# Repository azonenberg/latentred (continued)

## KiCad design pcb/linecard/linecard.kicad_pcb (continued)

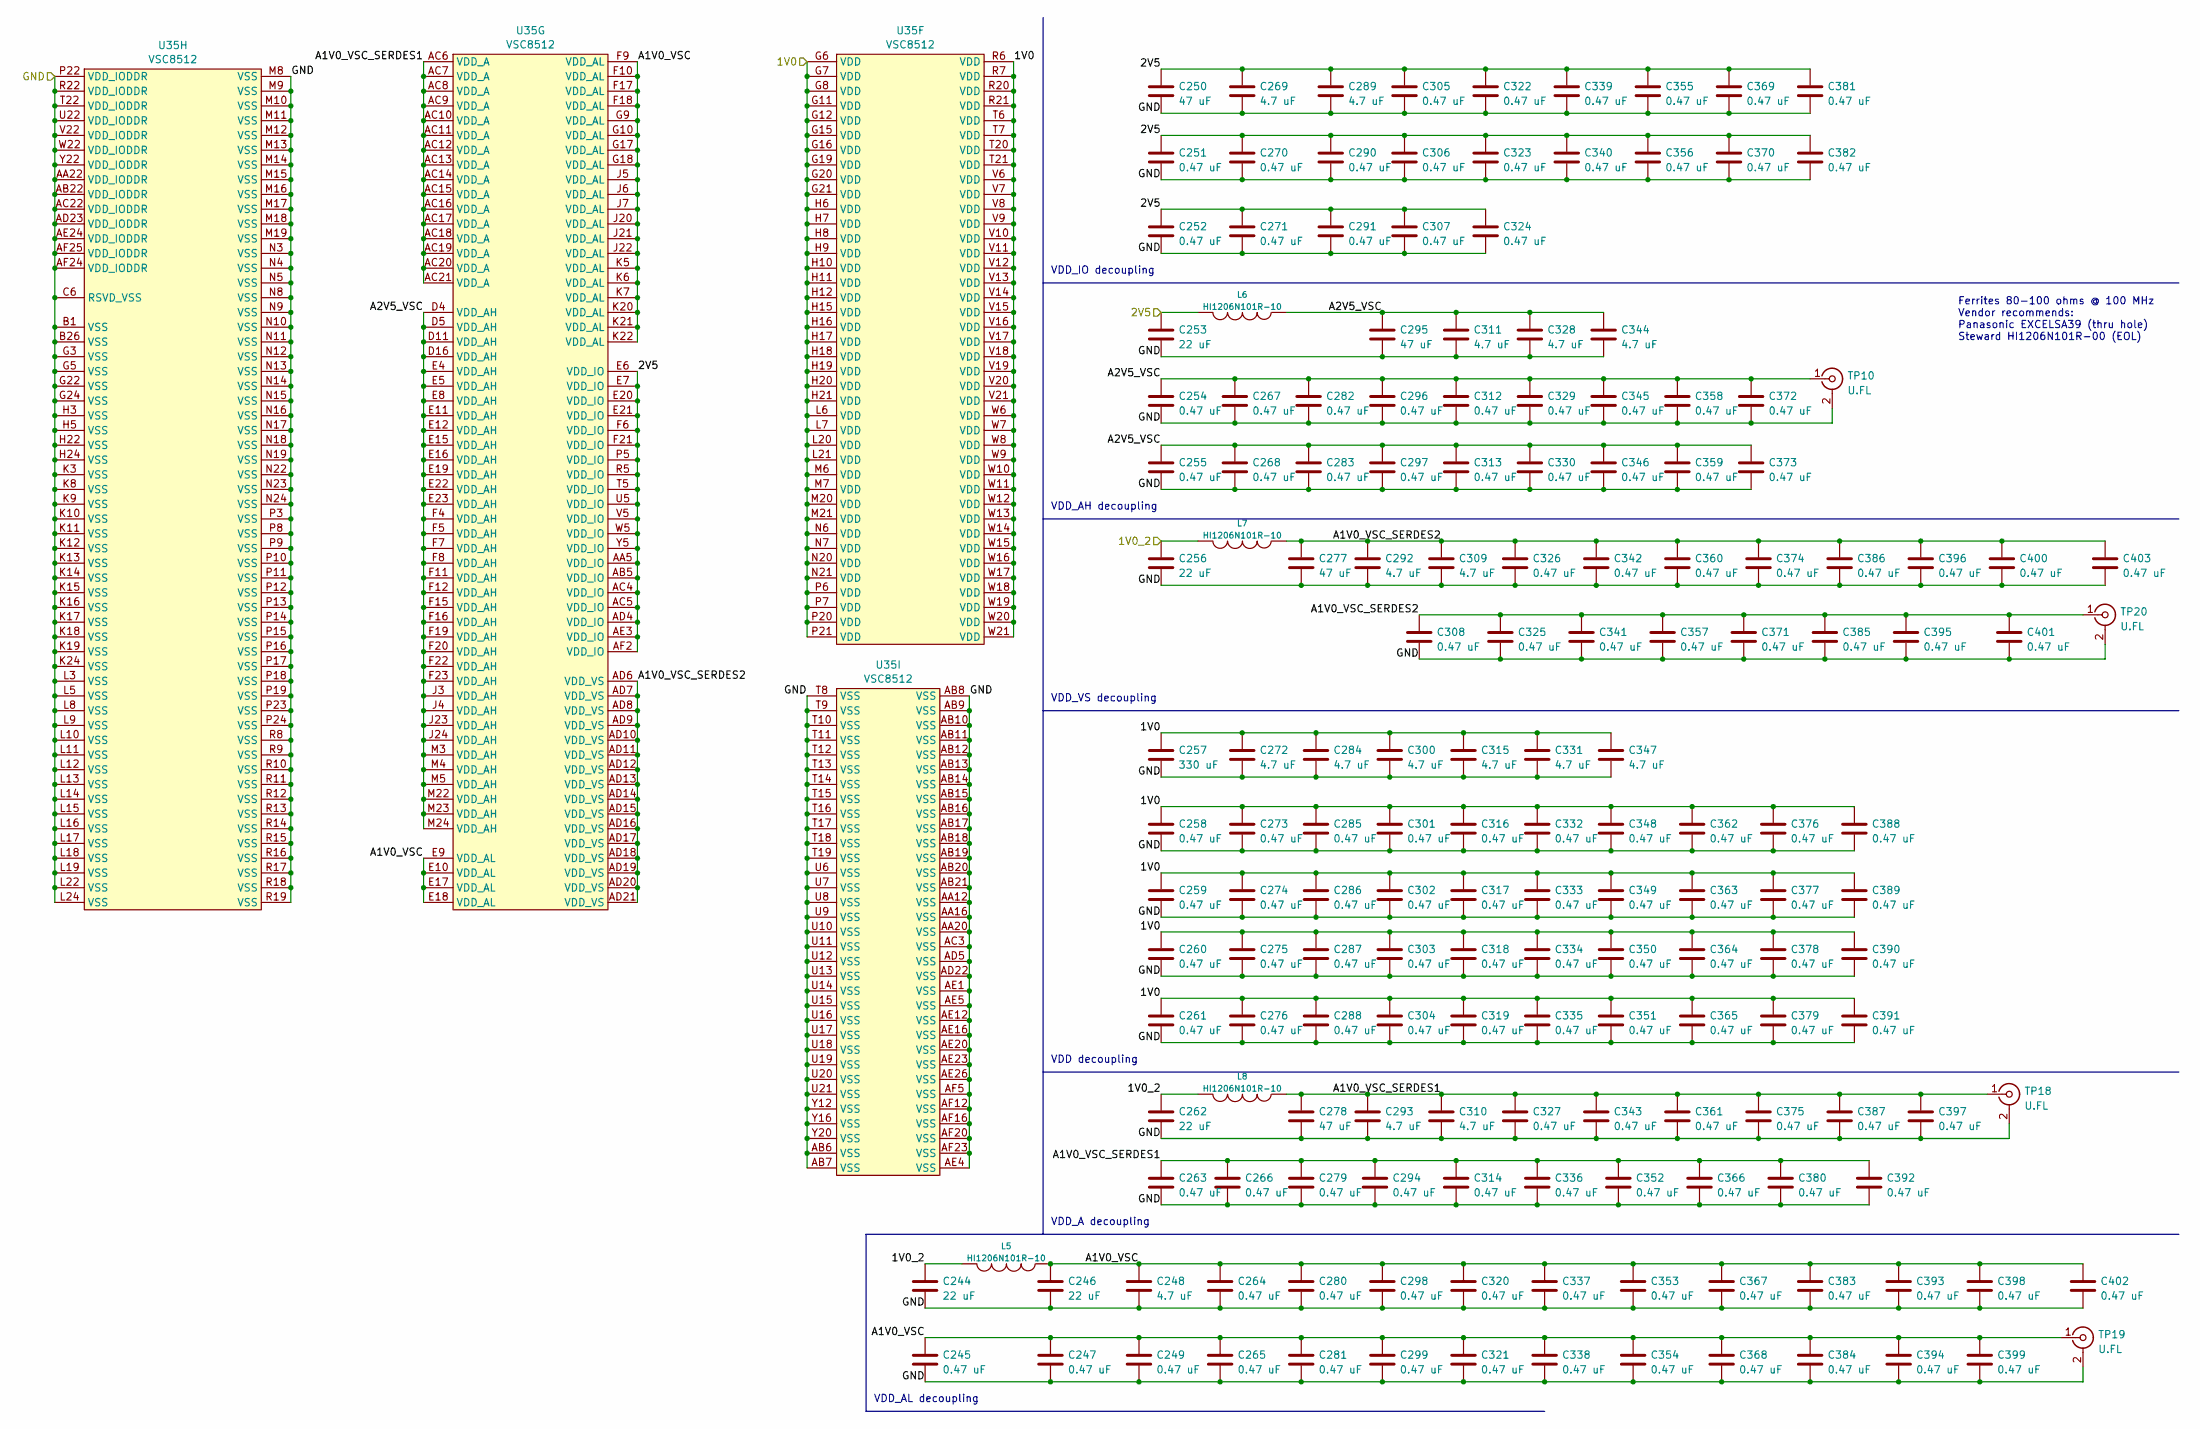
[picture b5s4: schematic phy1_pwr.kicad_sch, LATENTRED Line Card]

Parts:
C244, C246, C256, C262: 22 uF; EIA_0805_CAP_NOSILK
C245, C247, C249, C251, C252, C254, C255, C258, C259, C260, C261, C263, C264, C265, C266, C267, C268, C270, C271, C273, C274, C275, C276, C279, C280, C281, C282, C283, C285, C286, C287, C288, C290, C291, C294, C296, C297, C298, C299, C301, C302, C303, C304, C305, C306, C307, C308, C312, C313, C314, C316, C317, C318, C319, C320, C321, C322, C323, C324, C325, C326, C327, C329, C330, C332, C333, C334, C335, C336, C337, C338, C339, C340, C341, C342, C343, C345, C346, C348, C349, C350, C351, C352, C353, C354, C355, C356, C357, C358, C359, C360, C361, C362, C363, C364, C365, C366, C367, C368, C369, C370, C371, C372, C373, C374, C375, C376, C377, C378, C379, C380, C381, C382, C383, C384, C385, C386, C387, C388, C389, C390, C391, C392, C393, C394, C395, C396, C397, C398, C399, C400, C401, C402, C403: 0.47 uF; EIA_0402_CAP_NOSILK
C248, C269, C272, C284, C289, C292, C293, C300, C309, C310, C311, C315, C328, C331, C344, C347: 4.7 uF; EIA_0603_CAP_NOSILK
C250, C277, C295: 47 uF; EIA_1210_CAP_NOSILK
C253: 22 uF; EIA_1206_CAP_NOSILK
C257: 330 uF; EIA_1210_CAP_NOSILK
C278: 47 uF; EIA_1206_CAP_NOSILK
L5, L6, L7, L8: HI1206N101R-10; EIA_1206_CAP_NOSILK
TP10, TP18, TP19, TP20: U.FL; CONN_U.FL_TE_1909763-1
U35: VSC8512; BGA_676_27x27_FULLARRAY_1MM_FFG676

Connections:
/1V0: C257.1, C258.1, C259.1, C260.1, C261.1, C272.1, C273.1, C274.1, C275.1, C276.1, C284.1, C285.1, C286.1, C287.1, C288.1, C300.1, C301.1, C302.1, C303.1, C304.1, C315.1, C316.1, C317.1, C318.1, C319.1, C331.1, C332.1, C333.1, C334.1, C335.1, C347.1, C348.1, C349.1, C350.1, C351.1, C362.1, C363.1, C364.1, C365.1, C376.1, C377.1, C378.1, C379.1, C388.1, C389.1, C390.1, C391.1, U35.G6 (VDD), U35.G7 (VDD), U35.G8 (VDD), U35.G11 (VDD), U35.G12 (VDD), U35.G15 (VDD), U35.G16 (VDD), U35.G19 (VDD), U35.G20 (VDD), U35.G21 (VDD), U35.H6 (VDD), U35.H7 (VDD), U35.H8 (VDD), U35.H9 (VDD), U35.H10 (VDD), U35.H11 (VDD), U35.H12 (VDD), U35.H15 (VDD), U35.H16 (VDD), U35.H17 (VDD), U35.H18 (VDD), U35.H19 (VDD), U35.H20 (VDD), U35.H21 (VDD), U35.L6 (VDD), U35.L7 (VDD), U35.L20 (VDD), U35.L21 (VDD), U35.M6 (VDD), U35.M7 (VDD), U35.M20 (VDD), U35.M21 (VDD), U35.N6 (VDD), U35.N7 (VDD), U35.N20 (VDD), U35.N21 (VDD), U35.P6 (VDD), U35.P7 (VDD), U35.P20 (VDD), U35.P21 (VDD), U35.R6 (VDD), U35.R7 (VDD), U35.R20 (VDD), U35.R21 (VDD), U35.T6 (VDD), U35.T7 (VDD), U35.T20 (VDD), U35.T21 (VDD), U35.V6 (VDD), U35.V7 (VDD), U35.V8 (VDD), U35.V9 (VDD), U35.V10 (VDD), U35.V11 (VDD), U35.V12 (VDD), U35.V13 (VDD), U35.V14 (VDD), U35.V15 (VDD), U35.V16 (VDD), U35.V17 (VDD), U35.V18 (VDD), U35.V19 (VDD), U35.V20 (VDD), U35.V21 (VDD), U35.W6 (VDD), U35.W7 (VDD), U35.W8 (VDD), U35.W9 (VDD), U35.W10 (VDD), U35.W11 (VDD), U35.W12 (VDD), U35.W13 (VDD), U35.W14 (VDD), U35.W15 (VDD), U35.W16 (VDD), U35.W17 (VDD), U35.W18 (VDD), U35.W19 (VDD), U35.W20 (VDD), U35.W21 (VDD); also elsewhere on the board
/1V0_2: C244.1, C256.1, C262.1, L5.2, L7.2, L8.2; also elsewhere on the board
/2V5: C250.1, C251.1, C252.1, C253.1, C269.1, C270.1, C271.1, C289.1, C290.1, C291.1, C305.1, C306.1, C307.1, C322.1, C323.1, C324.1, C339.1, C340.1, C355.1, C356.1, C369.1, C370.1, C381.1, C382.1, L6.2, U35.AA5 (VDD_IO), U35.AB5 (VDD_IO), U35.AC4 (VDD_IO), U35.AC5 (VDD_IO), U35.AD4 (VDD_IO), U35.AE3 (VDD_IO), U35.AF2 (VDD_IO), U35.E6 (VDD_IO), U35.E7 (VDD_IO), U35.E20 (VDD_IO), U35.E21 (VDD_IO), U35.F6 (VDD_IO), U35.F21 (VDD_IO), U35.P5 (VDD_IO), U35.R5 (VDD_IO), U35.T5 (VDD_IO), U35.U5 (VDD_IO), U35.V5 (VDD_IO), U35.W5 (VDD_IO), U35.Y5 (VDD_IO); also elsewhere on the board
/PHY 1 Power/A1V0_VSC: C245.1, C246.1, C247.1, C248.1, C249.1, C264.1, C265.1, C280.1, C281.1, C298.1, C299.1, C320.1, C321.1, C337.1, C338.1, C353.1, C354.1, C367.1, C368.1, C383.1, C384.1, C393.1, C394.1, C398.1, C399.1, C402.1, L5.1, TP19.1 (In), U35.E9 (VDD_AL), U35.E10 (VDD_AL), U35.E17 (VDD_AL), U35.E18 (VDD_AL), U35.F9 (VDD_AL), U35.F10 (VDD_AL), U35.F17 (VDD_AL), U35.F18 (VDD_AL), U35.G9 (VDD_AL), U35.G10 (VDD_AL), U35.G17 (VDD_AL), U35.G18 (VDD_AL), U35.J5 (VDD_AL), U35.J6 (VDD_AL), U35.J7 (VDD_AL), U35.J20 (VDD_AL), U35.J21 (VDD_AL), U35.J22 (VDD_AL), U35.K5 (VDD_AL), U35.K6 (VDD_AL), U35.K7 (VDD_AL), U35.K20 (VDD_AL), U35.K21 (VDD_AL), U35.K22 (VDD_AL)
/PHY 1 Power/A1V0_VSC_SERDES1: C263.1, C266.1, C278.1, C279.1, C293.1, C294.1, C310.1, C314.1, C327.1, C336.1, C343.1, C352.1, C361.1, C366.1, C375.1, C380.1, C387.1, C392.1, C397.1, L8.1, TP18.1 (In), U35.AC6 (VDD_A), U35.AC7 (VDD_A), U35.AC8 (VDD_A), U35.AC9 (VDD_A), U35.AC10 (VDD_A), U35.AC11 (VDD_A), U35.AC12 (VDD_A), U35.AC13 (VDD_A), U35.AC14 (VDD_A), U35.AC15 (VDD_A), U35.AC16 (VDD_A), U35.AC17 (VDD_A), U35.AC18 (VDD_A), U35.AC19 (VDD_A), U35.AC20 (VDD_A), U35.AC21 (VDD_A)
/PHY 1 Power/A1V0_VSC_SERDES2: C277.1, C292.1, C308.1, C309.1, C325.1, C326.1, C341.1, C342.1, C357.1, C360.1, C371.1, C374.1, C385.1, C386.1, C395.1, C396.1, C400.1, C401.1, C403.1, L7.1, TP20.1 (In), U35.AD6 (VDD_VS), U35.AD7 (VDD_VS), U35.AD8 (VDD_VS), U35.AD9 (VDD_VS), U35.AD10 (VDD_VS), U35.AD11 (VDD_VS), U35.AD12 (VDD_VS), U35.AD13 (VDD_VS), U35.AD14 (VDD_VS), U35.AD15 (VDD_VS), U35.AD16 (VDD_VS), U35.AD17 (VDD_VS), U35.AD18 (VDD_VS), U35.AD19 (VDD_VS), U35.AD20 (VDD_VS), U35.AD21 (VDD_VS)
/PHY 1 Power/A2V5_VSC: C254.1, C255.1, C267.1, C268.1, C282.1, C283.1, C295.1, C296.1, C297.1, C311.1, C312.1, C313.1, C328.1, C329.1, C330.1, C344.1, C345.1, C346.1, C358.1, C359.1, C372.1, C373.1, L6.1, TP10.1 (In), U35.D4 (VDD_AH), U35.D5 (VDD_AH), U35.D11 (VDD_AH), U35.D16 (VDD_AH), U35.E4 (VDD_AH), U35.E5 (VDD_AH), U35.E8 (VDD_AH), U35.E11 (VDD_AH), U35.E12 (VDD_AH), U35.E15 (VDD_AH), U35.E16 (VDD_AH), U35.E19 (VDD_AH), U35.E22 (VDD_AH), U35.E23 (VDD_AH), U35.F4 (VDD_AH), U35.F5 (VDD_AH), U35.F7 (VDD_AH), U35.F8 (VDD_AH), U35.F11 (VDD_AH), U35.F12 (VDD_AH), U35.F15 (VDD_AH), U35.F16 (VDD_AH), U35.F19 (VDD_AH), U35.F20 (VDD_AH), U35.F22 (VDD_AH), U35.F23 (VDD_AH), U35.J3 (VDD_AH), U35.J4 (VDD_AH), U35.J23 (VDD_AH), U35.J24 (VDD_AH), U35.M3 (VDD_AH), U35.M4 (VDD_AH), U35.M5 (VDD_AH), U35.M22 (VDD_AH), U35.M23 (VDD_AH), U35.M24 (VDD_AH)

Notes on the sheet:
VDD_AL decoupling
VDD decoupling
VDD_A decoupling
Ferrites 80-100 ohms @ 100 MHz Vendor recommends: Panasonic EXCELSA39 (thru hole) Steward HI1206N101R-00 (EOL)
VDD_VS decoupling
VDD_AH decoupling
VDD_IO decoupling

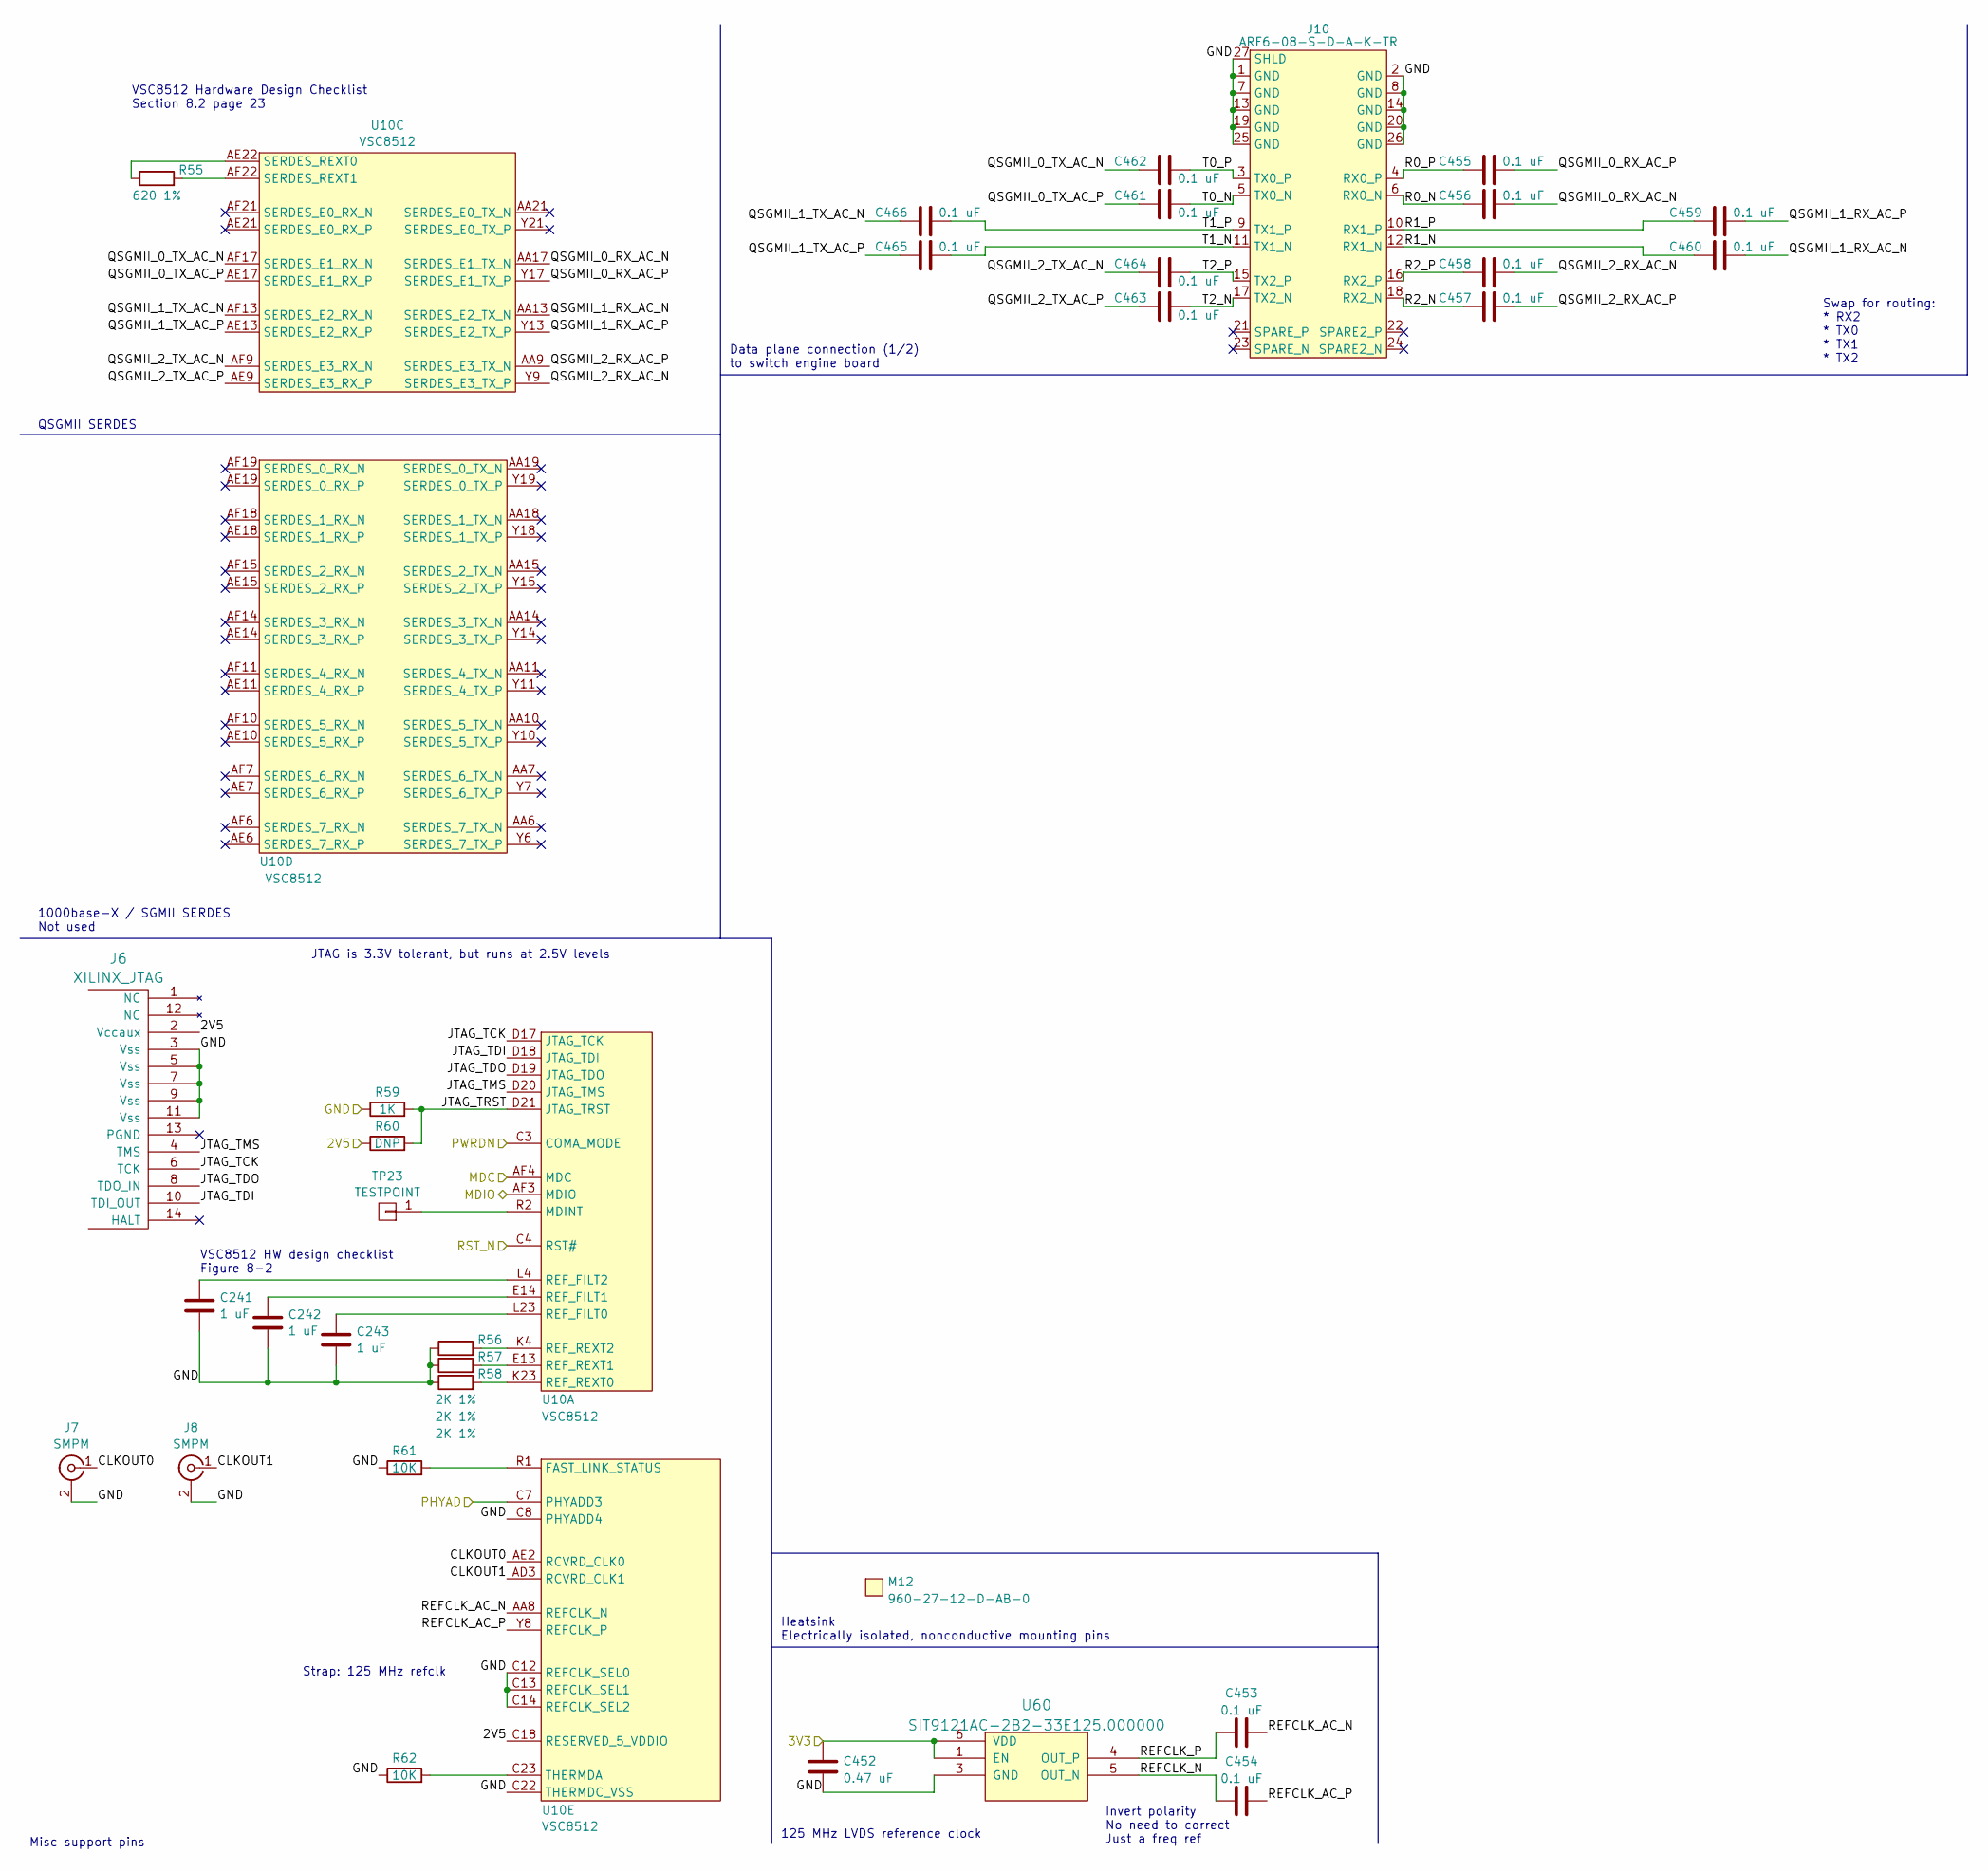
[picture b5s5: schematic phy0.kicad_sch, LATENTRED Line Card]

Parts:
C241, C242, C243: 1 uF; EIA_0402_CAP_NOSILK
C452: 0.47 uF; EIA_0402_CAP_NOSILK
C453, C454, C455, C456, C457, C458, C459, C460, C461, C462, C463, C464, C465, C466: 0.1 uF; EIA_0402_CAP_NOSILK
J6: XILINX_JTAG; XILINX_JTAG_PTH_MOLEX_0878311420
J7, J8: SMPM; CONN_SMPM_AMPHENOL_C925-197J-51PT
J10: ARF6-08-S-D-A-K-TR; CONN_SAMTEC_ARF6-08-S-D-A-K-TR
M12: 960-27-12-D-AB-0; HEATSINK_WAKEFIELDVETTE_960-27-12-D-AB-0
R55: 620 1%; EIA_0402_RES_NOSILK
R56, R57, R58: 2K 1%; EIA_0402_RES_NOSILK
R59: 1K; EIA_0402_RES_NOSILK
R60: DNP; EIA_0402_RES_NOSILK
R61, R62: 10K; EIA_0402_RES_NOSILK
TP23: TESTPOINT; TESTPOINT_SMT_0.5MM
U10: VSC8512; BGA_676_27x27_FULLARRAY_1MM_FFG676
U60: SIT9121AC-2B2-33E125.000000; OSCILLATOR_LVDS_3.2x2.5

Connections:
/2V5: J6.2 (Vccaux), R60.1, U10.C18 (RESERVED_5_VDDIO); also elsewhere on the board
/3V3: C452.1, U60.1 (EN), U60.6 (VDD); also elsewhere on the board
/MDC: U10.AF4 (MDC); also elsewhere on the board
/MDIO: U10.AF3 (MDIO); also elsewhere on the board
/PHY0_PWRDN: U10.C3 (COMA_MODE); also elsewhere on the board
/PHY0_RST_N: U10.C4 (RST#); also elsewhere on the board
/PHY 0 Backend/CLKOUT0: J7.1 (In), U10.AE2 (RCVRD_CLK0)
/PHY 0 Backend/CLKOUT1: J8.1 (In), U10.AD3 (RCVRD_CLK1)
/PHY 0 Backend/JTAG_TCK: J6.6 (TCK), U10.D17 (JTAG_TCK)
/PHY 0 Backend/JTAG_TDI: J6.10 (TDI_OUT), U10.D18 (JTAG_TDI)
/PHY 0 Backend/JTAG_TDO: J6.8 (TDO_IN), U10.D19 (JTAG_TDO)
/PHY 0 Backend/JTAG_TMS: J6.4 (TMS), U10.D20 (JTAG_TMS)
/PHY 0 Backend/JTAG_TRST: R59.2, R60.2, U10.D21 (JTAG_TRST)
/PHY 0 Backend/QSGMII_0_RX_AC_N: C456.2, U10.AA17 (SERDES_E1_TX_N)
/PHY 0 Backend/QSGMII_0_RX_AC_P: C455.2, U10.Y17 (SERDES_E1_TX_P)
/PHY 0 Backend/QSGMII_0_TX_AC_N: C462.1, U10.AF17 (SERDES_E1_RX_N)
/PHY 0 Backend/QSGMII_0_TX_AC_P: C461.1, U10.AE17 (SERDES_E1_RX_P)
/PHY 0 Backend/QSGMII_1_RX_AC_N: C460.2, U10.AA13 (SERDES_E2_TX_N)
/PHY 0 Backend/QSGMII_1_RX_AC_P: C459.2, U10.Y13 (SERDES_E2_TX_P)
/PHY 0 Backend/QSGMII_1_TX_AC_N: C466.1, U10.AF13 (SERDES_E2_RX_N)
/PHY 0 Backend/QSGMII_1_TX_AC_P: C465.1, U10.AE13 (SERDES_E2_RX_P)
/PHY 0 Backend/QSGMII_2_RX_AC_N: C458.2, U10.Y9 (SERDES_E3_TX_P)
/PHY 0 Backend/QSGMII_2_RX_AC_P: C457.2, U10.AA9 (SERDES_E3_TX_N)
/PHY 0 Backend/QSGMII_2_TX_AC_N: C464.1, U10.AF9 (SERDES_E3_RX_N)
/PHY 0 Backend/QSGMII_2_TX_AC_P: C463.1, U10.AE9 (SERDES_E3_RX_P)
/PHY 0 Backend/R0_N: C456.1, J10.6 (RX0_N)
/PHY 0 Backend/R0_P: C455.1, J10.4 (RX0_P)
/PHY 0 Backend/R1_N: C460.1, J10.12 (RX1_N)
/PHY 0 Backend/R1_P: C459.1, J10.10 (RX1_P)
/PHY 0 Backend/R2_N: C457.1, J10.18 (RX2_N)
/PHY 0 Backend/R2_P: C458.1, J10.16 (RX2_P)
/PHY 0 Backend/REFCLK_AC_N: C453.2, U10.AA8 (REFCLK_N)
/PHY 0 Backend/REFCLK_AC_P: C454.2, U10.Y8 (REFCLK_P)
/PHY 0 Backend/REFCLK_N: C454.1, U60.5 (OUT_N)
/PHY 0 Backend/REFCLK_P: C453.1, U60.4 (OUT_P)
/PHY 0 Backend/T0_N: C461.2, J10.5 (TX0_N)
/PHY 0 Backend/T0_P: C462.2, J10.3 (TX0_P)
/PHY 0 Backend/T1_N: C465.2, J10.11 (TX1_N)
/PHY 0 Backend/T1_P: C466.2, J10.9 (TX1_P)
/PHY 0 Backend/T2_N: C463.2, J10.17 (TX2_N)
/PHY 0 Backend/T2_P: C464.2, J10.15 (TX2_P)
unnamed: TP23.1, U10.R2 (MDINT)
unnamed: C243.1, U10.L23 (REF_FILT0)
unnamed: C242.1, U10.E14 (REF_FILT1)
unnamed: C241.1, U10.L4 (REF_FILT2)
unnamed: R58.2, U10.K23 (REF_REXT0)
unnamed: R57.2, U10.E13 (REF_REXT1)
unnamed: R56.2, U10.K4 (REF_REXT2)
unnamed: R55.1, U10.AE22 (SERDES_REXT0)
unnamed: R55.2, U10.AF22 (SERDES_REXT1)
unnamed: R61.2, U10.R1 (FAST_LINK_STATUS)
unnamed: R62.2, U10.C23 (THERMDA)

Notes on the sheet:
JTAG is 3.3V tolerant, but runs at 2.5V levels
Swap for routing: * RX2 * TX0 * TX1 * TX2
VSC8512 HW design checklist Figure 8-2
Misc support pins
Heatsink Electrically isolated, nonconductive mounting pins
QSGMII SERDES
Strap: 125 MHz refclk
VSC8512 Hardware Design Checklist Section 8.2 page 23
125 MHz LVDS reference clock
Invert polarity No need to correct Just a freq ref
Data plane connection (1/2) to switch engine board
1000base-X / SGMII SERDES Not used

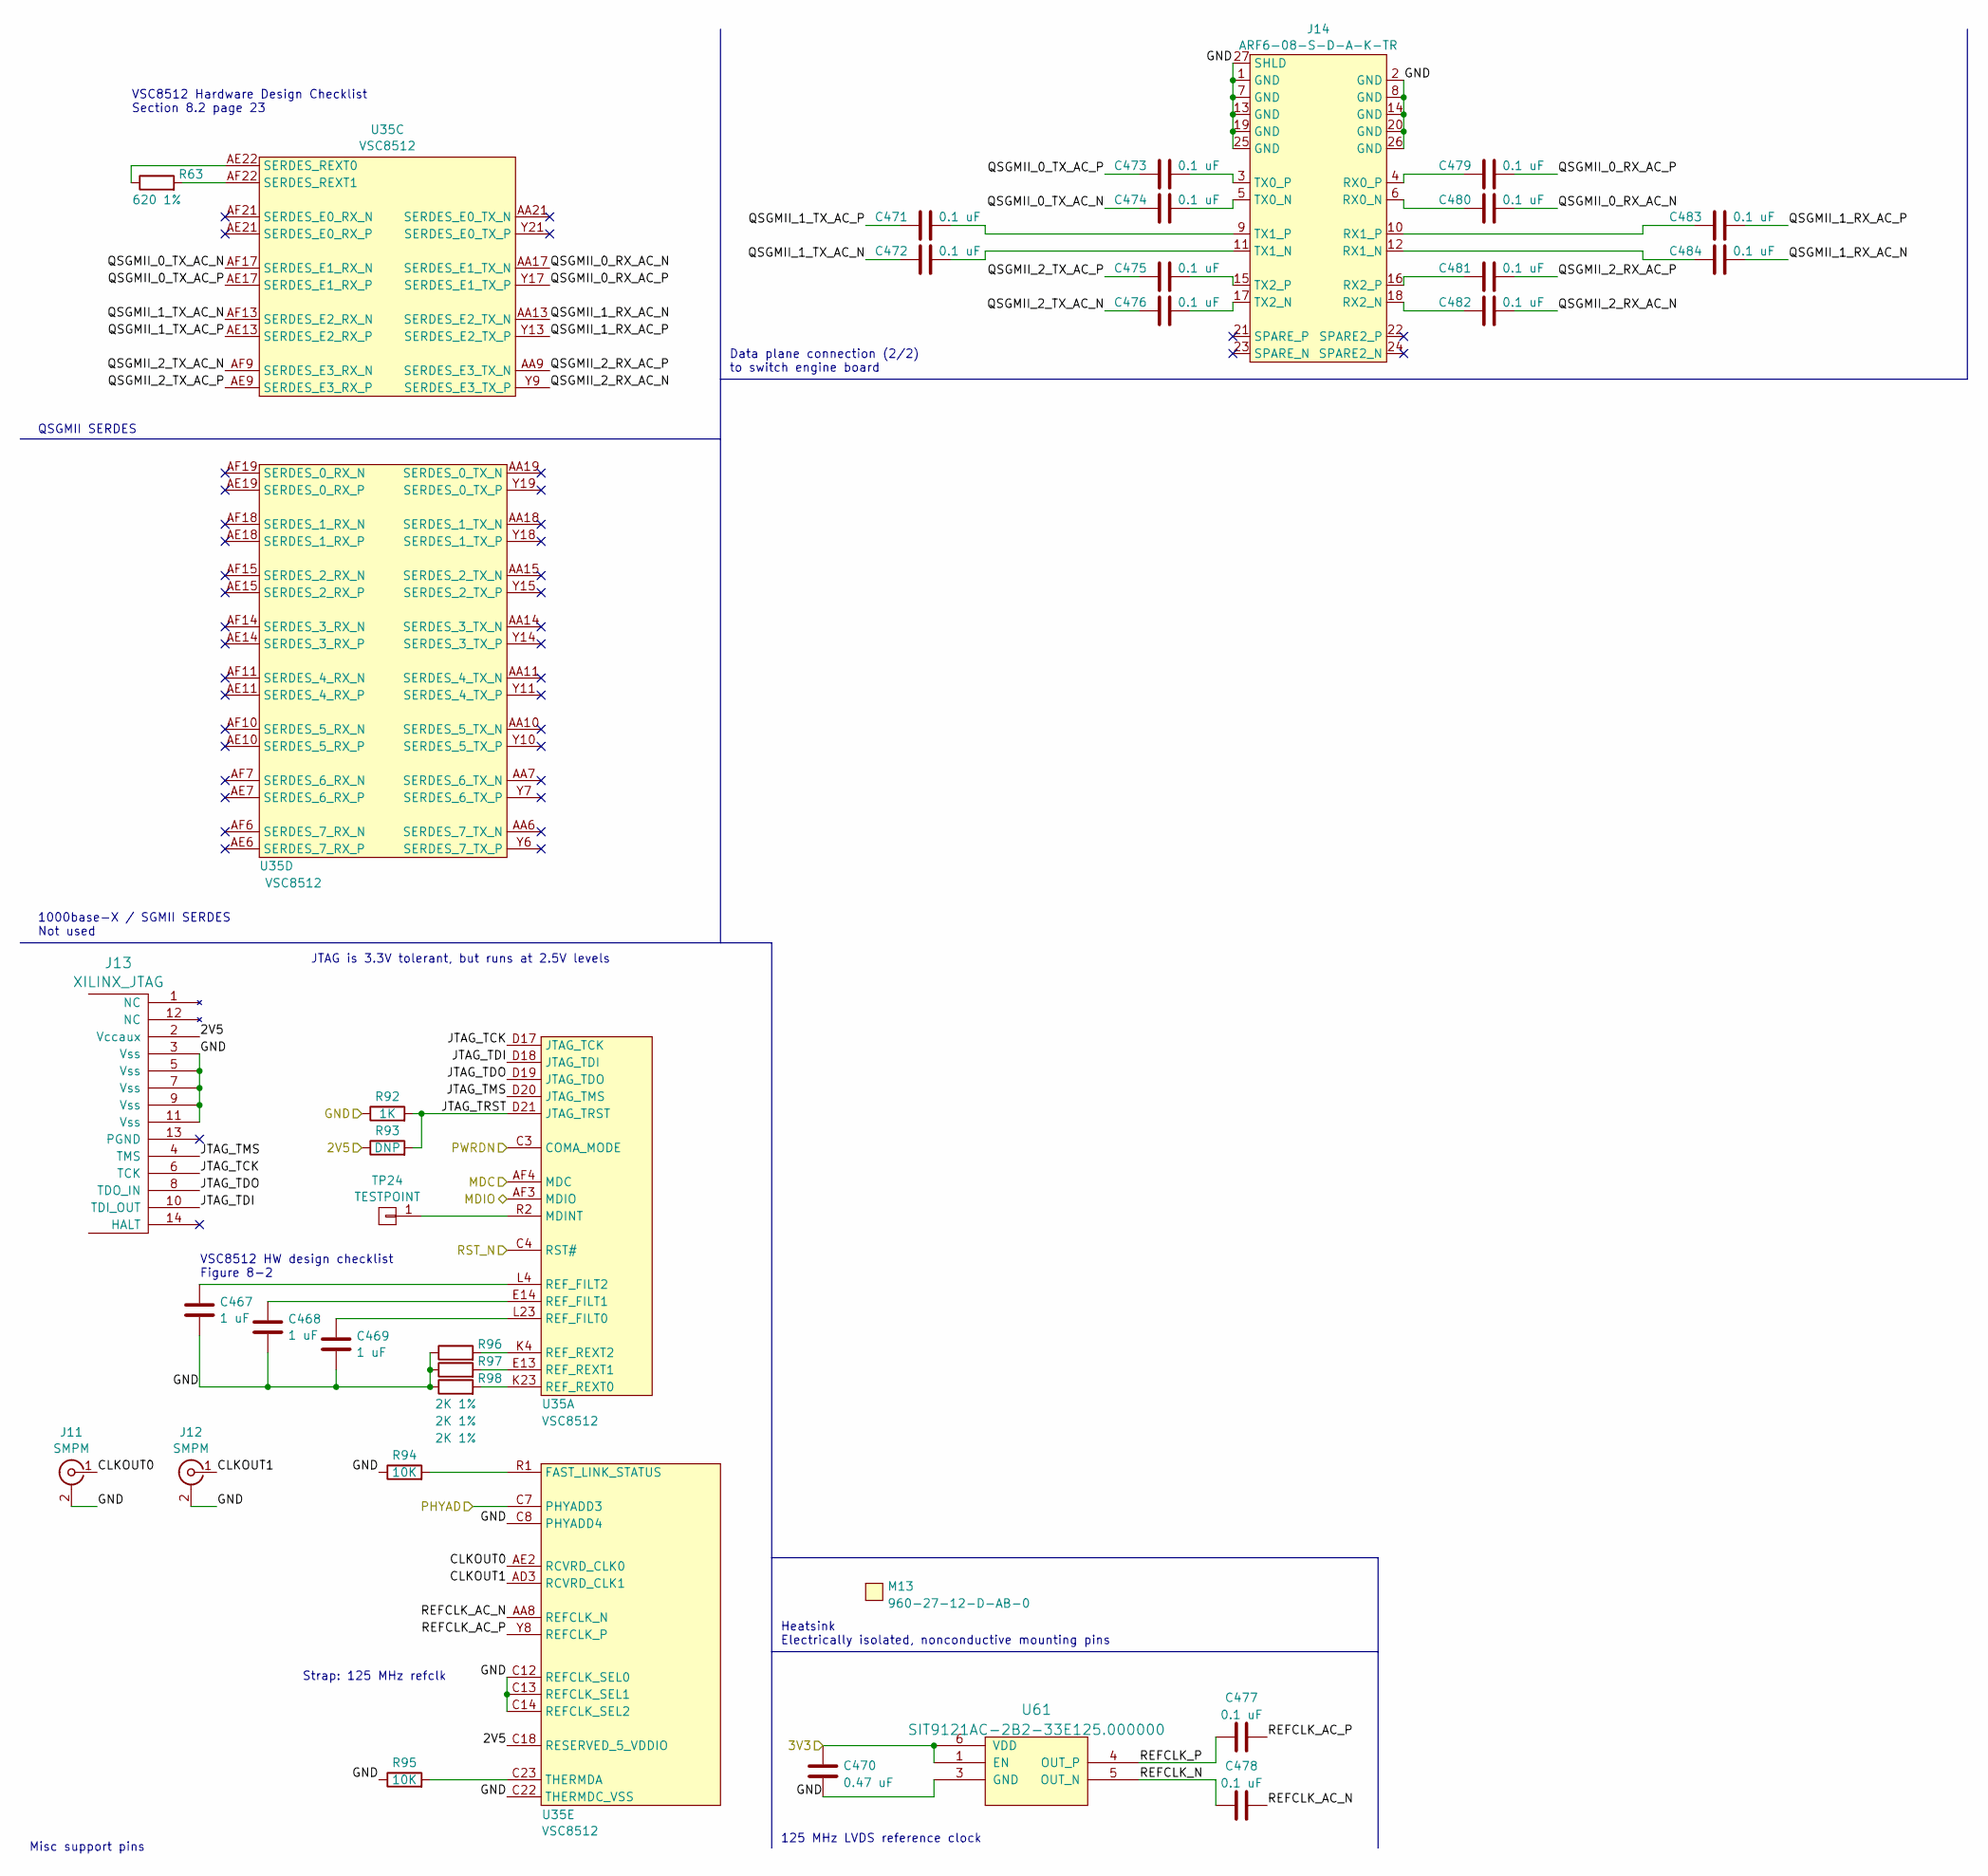
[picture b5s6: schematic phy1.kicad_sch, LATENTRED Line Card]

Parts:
C467, C468, C469: 1 uF; EIA_0402_CAP_NOSILK
C470: 0.47 uF; EIA_0402_CAP_NOSILK
C471, C472, C473, C474, C475, C476, C477, C478, C479, C480, C481, C482, C483, C484: 0.1 uF; EIA_0402_CAP_NOSILK
J11, J12: SMPM; CONN_SMPM_AMPHENOL_C925-197J-51PT
J13: XILINX_JTAG; XILINX_JTAG_PTH_MOLEX_0878311420
J14: ARF6-08-S-D-A-K-TR; CONN_SAMTEC_ARF6-08-S-D-A-K-TR
M13: 960-27-12-D-AB-0; HEATSINK_WAKEFIELDVETTE_960-27-12-D-AB-0
R63: 620 1%; EIA_0402_RES_NOSILK
R92: 1K; EIA_0402_RES_NOSILK
R93: DNP; EIA_0402_RES_NOSILK
R94, R95: 10K; EIA_0402_RES_NOSILK
R96, R97, R98: 2K 1%; EIA_0402_RES_NOSILK
TP24: TESTPOINT; TESTPOINT_SMT_0.5MM
U35: VSC8512; BGA_676_27x27_FULLARRAY_1MM_FFG676
U61: SIT9121AC-2B2-33E125.000000; OSCILLATOR_LVDS_3.2x2.5

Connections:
/2V5: J13.2 (Vccaux), R93.1, U35.C7 (PHYADD3), U35.C18 (RESERVED_5_VDDIO); also elsewhere on the board
/3V3: C470.1, U61.1 (EN), U61.6 (VDD); also elsewhere on the board
/MDC: U35.AF4 (MDC); also elsewhere on the board
/MDIO: U35.AF3 (MDIO); also elsewhere on the board
/PHY1_PWRDN: U35.C3 (COMA_MODE); also elsewhere on the board
/PHY1_RST_N: U35.C4 (RST#); also elsewhere on the board
/PHY 1 Backend/CLKOUT0: J11.1 (In), U35.AE2 (RCVRD_CLK0)
/PHY 1 Backend/CLKOUT1: J12.1 (In), U35.AD3 (RCVRD_CLK1)
/PHY 1 Backend/JTAG_TCK: J13.6 (TCK), U35.D17 (JTAG_TCK)
/PHY 1 Backend/JTAG_TDI: J13.10 (TDI_OUT), U35.D18 (JTAG_TDI)
/PHY 1 Backend/JTAG_TDO: J13.8 (TDO_IN), U35.D19 (JTAG_TDO)
/PHY 1 Backend/JTAG_TMS: J13.4 (TMS), U35.D20 (JTAG_TMS)
/PHY 1 Backend/JTAG_TRST: R92.2, R93.2, U35.D21 (JTAG_TRST)
/PHY 1 Backend/QSGMII_0_RX_AC_N: C480.2, U35.AA17 (SERDES_E1_TX_N)
/PHY 1 Backend/QSGMII_0_RX_AC_P: C479.2, U35.Y17 (SERDES_E1_TX_P)
/PHY 1 Backend/QSGMII_0_TX_AC_N: C474.1, U35.AF17 (SERDES_E1_RX_N)
/PHY 1 Backend/QSGMII_0_TX_AC_P: C473.1, U35.AE17 (SERDES_E1_RX_P)
/PHY 1 Backend/QSGMII_1_RX_AC_N: C484.2, U35.AA13 (SERDES_E2_TX_N)
/PHY 1 Backend/QSGMII_1_RX_AC_P: C483.2, U35.Y13 (SERDES_E2_TX_P)
/PHY 1 Backend/QSGMII_1_TX_AC_N: C472.1, U35.AF13 (SERDES_E2_RX_N)
/PHY 1 Backend/QSGMII_1_TX_AC_P: C471.1, U35.AE13 (SERDES_E2_RX_P)
/PHY 1 Backend/QSGMII_2_RX_AC_N: C482.2, U35.Y9 (SERDES_E3_TX_P)
/PHY 1 Backend/QSGMII_2_RX_AC_P: C481.2, U35.AA9 (SERDES_E3_TX_N)
/PHY 1 Backend/QSGMII_2_TX_AC_N: C476.1, U35.AF9 (SERDES_E3_RX_N)
/PHY 1 Backend/QSGMII_2_TX_AC_P: C475.1, U35.AE9 (SERDES_E3_RX_P)
/PHY 1 Backend/REFCLK_AC_N: C478.2, U35.AA8 (REFCLK_N)
/PHY 1 Backend/REFCLK_AC_P: C477.2, U35.Y8 (REFCLK_P)
/PHY 1 Backend/REFCLK_N: C478.1, U61.5 (OUT_N)
/PHY 1 Backend/REFCLK_P: C477.1, U61.4 (OUT_P)
unnamed: C480.1, J14.6 (RX0_N)
unnamed: C479.1, J14.4 (RX0_P)
unnamed: C484.1, J14.12 (RX1_N)
unnamed: C483.1, J14.10 (RX1_P)
unnamed: C482.1, J14.18 (RX2_N)
unnamed: C481.1, J14.16 (RX2_P)
unnamed: C474.2, J14.5 (TX0_N)
unnamed: C473.2, J14.3 (TX0_P)
unnamed: C472.2, J14.11 (TX1_N)
unnamed: C471.2, J14.9 (TX1_P)
unnamed: C476.2, J14.17 (TX2_N)
unnamed: C475.2, J14.15 (TX2_P)
unnamed: TP24.1, U35.R2 (MDINT)
unnamed: C469.1, U35.L23 (REF_FILT0)
unnamed: C468.1, U35.E14 (REF_FILT1)
unnamed: C467.1, U35.L4 (REF_FILT2)
unnamed: R98.2, U35.K23 (REF_REXT0)
unnamed: R97.2, U35.E13 (REF_REXT1)
unnamed: R96.2, U35.K4 (REF_REXT2)
unnamed: R63.1, U35.AE22 (SERDES_REXT0)
unnamed: R63.2, U35.AF22 (SERDES_REXT1)
unnamed: R94.2, U35.R1 (FAST_LINK_STATUS)
unnamed: R95.2, U35.C23 (THERMDA)

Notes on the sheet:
Data plane connection (2/2) to switch engine board
QSGMII SERDES
Misc support pins
1000base-X / SGMII SERDES Not used
Strap: 125 MHz refclk
JTAG is 3.3V tolerant, but runs at 2.5V levels
125 MHz LVDS reference clock
VSC8512 Hardware Design Checklist Section 8.2 page 23
Heatsink Electrically isolated, nonconductive mounting pins
VSC8512 HW design checklist Figure 8-2
